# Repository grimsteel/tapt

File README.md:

# tapt

> just a button

`tapt` is a BLE-powered IoT button. It uses an nRF52810 and can be powered for long periods of time on a single CR2032 battery.

It can be connected to Home Assistant and hooked up to automations from there.

## Usage

> Note: do NOT connect the battery when the board is powered on the debug header.

### Assembly

1. The 5 pin debug header must be soldered on for flashing
2. The battery holder can be soldered onto the back 
3. The WS2812B and the UART are optional. Both of these will cause more battery drain.
4. The PCB can be screwed into the base of the case. The button cap locks into the case.

### Flashing

> Note: An nRF-SDK environment is required. This is a *freestanding project*

1. Customize the device ID and board name if needed in `prj.conf`
1. Build the firmware:
   ```sh
   west build -b tapt -- -DBOARD_ROOT=.
   ```
1. Flash the nRF over SWD, using the SWD header on the board. The pins are labeled on the bottom.

   Firmware is included in the `./firmware` directory.
3. Profit. The button should be autodiscovered in Home Assistant, where it will expose a button entity.

## Purpose

I made this because I wanted a large button for controlling random automations.

I also wanted to learn more about RF PCB design, and the nRF chip was a great place to start.

## Schematic + PCB

| F.Cu                         | In1.Cu                       | In2.Cu                       | B.Cu                         |
|------------------------------|------------------------------|------------------------------|------------------------------|
|  |  |  |  |
|                              |                              |                              |                              |

## Case

Apart from the PCB, tapt just has two components: the base and the button. 

The PCB is screwed into the base, and the button sits inside the base. When pressed down, it presses the limit switch.

[Onshape link](https://cad.onshape.com/documents/617a57c855f6b668c2d4cd24/w/013e725e8d7df515c4261645/e/6602b3eddf1a670923f88f78)

## Bill of Materials

[BOM CSV](./bom.csv)

If the price is 0, I have the component already (basically everything except the PCB/PCBA). I added links for reference, though

| Description            | Part ID  | Link                                                 | Per-unit price | Board Quantity | Total Quantity | Extended? | Total Price | Running Price w/ Tax |
|------------------------|----------|------------------------------------------------------|----------------|----------------|----------------|-----------|-------------|----------------------|
| 2.4 GHz Chip Antenna   | C89334   | https://jlcpcb.com/partdetail/C89334                 | $0.62          | 1              | 5              | TRUE      | $6.1630     | $6.69                |
| 100nF Capacitor        | C1525    | https://jlcpcb.com/partdetail/C1525                  | $0.00          | 4              | 8              | FALSE     | $0.0104     | $6.70                |
| 0.8pF Capacitor        | C88902   | https://jlcpcb.com/partdetail/C88902                 | $0.04          | 1              | 20             | TRUE      | $3.7420     | $10.76               |
| 1.0pF Capacitor        | C1550    | https://jlcpcb.com/partdetail/C1550                  | $0.00          | 1              | 20             | FALSE     | $0.0240     | $10.79               |
| 100pF Capacitor        | C1546    | https://jlcpcb.com/partdetail/C1546                  | $0.00          | 1              | 2              | FALSE     | $0.0024     | $10.79               |
| 1uF Capacitor          | C28323   | https://jlcpcb.com/partdetail/C28323                 | $0.01          | 1              | 2              | FALSE     | $0.0254     | $10.82               |
| 12pF Capacitor         | C1547    | https://jlcpcb.com/partdetail/C1547                  | $0.00          | 4              | 8              | FALSE     | $0.0096     | $10.83               |
| 4.7uF Capacitor        | C19666   | https://jlcpcb.com/partdetail/C19666                 | $0.01          | 1              | 2              | FALSE     | $0.0206     | $10.85               |
| Green LED              | C2297    | https://jlcpcb.com/partdetail/C2297                  | $0.02          | 1              | 2              | FALSE     | $0.0314     | $10.88               |
| 3.9nH Inductor         | C14033   | https://jlcpcb.com/partdetail/C14033                 | $0.00          | 2              | 20             | FALSE     | $0.0800     | $10.97               |
| 10uH Inductor          | C86083   | https://jlcpcb.com/partdetail/C86083                 | $0.05          | 1              | 6              | TRUE      | $3.3412     | $14.60               |
| 15nH Inductor          | C27143   | https://jlcpcb.com/partdetail/C27143                 | $0.05          | 1              | 20             | FALSE     | $1.0200     | $15.71               |
| 2.7nH Inductor         | C27123   | https://jlcpcb.com/partdetail/C27123                 | $0.00          | 1              | 20             | TRUE      | $3.1360     | $19.12               |
| 1k Resistor            | C11702   | https://jlcpcb.com/partdetail/C11702                 | $0.00          | 1              | 2              | FALSE     | $0.0014     | $19.12               |
| 100k Resistor          | C25741   | https://jlcpcb.com/partdetail/C25741                 | $0.00          | 1              | 2              | FALSE     | $0.0016     | $19.12               |
| 1M Resistor            | C26083   | https://jlcpcb.com/partdetail/C26083                 | $0.00          | 2              | 4              | FALSE     | $0.0032     | $19.12               |
| SW_SPST Button         | C720477  | https://jlcpcb.com/partdetail/C720477                | $0.05          | 1              | 2              | FALSE     | $0.1082     | $19.24               |
| nRF52810-QCxx          | C519278  | https://jlcpcb.com/partdetail/C519278                | $2.99          | 1              | 2              | TRUE      | $9.0228     | $29.04               |
| 32MHz Crystal          | C2965582 | https://jlcpcb.com/partdetail/C2965582               | $0.07          | 1              | 6              | TRUE      | $3.4606     | $32.80               |
| 32.768kHz Crystal      | C97603   | https://jlcpcb.com/partdetail/C97603                 | $0.24          | 1              | 5              | TRUE      | $4.2365     | $37.40               |
| PCB                    |          |                                                      | $1.00          |                | 2              |           | $2.00       | $39.57               |
| PCBA Fees              |          |                                                      | $11.55         |                | 1              |           | $11.55      | $52.12               |
| PCB Shipping           |          |                                                      | $3.12          |                | 1              |           | $3.12       | $55.51               |
| Case                   |          | 3d-printed                                           | $0.00          |                | 1              |           | $0.00       | $55.51               |
| M3 Heatset             |          | https://www.aliexpress.us/item/3256802711669116.html | $0.00          |                | 2              |           | $0.00       | $55.51               |
| M3 Screw x 8mm         |          | https://www.aliexpress.us/item/2255801013414226.html | $0.00          |                | 2              |           | $0.00       | $55.51               |
| SPDT Limit Switch      |          | https://www.aliexpress.us/item/2255800451734482.html | $0.00          |                | 1              |           | $0.00       | $55.51               |
| 2.54mm Pin Header 1x05 |          | https://www.aliexpress.us/item/3256806247917356.html | $0.00          |                | 1              |           | $0.00       | $55.51               |
| CR2032 Holder          |          | https://www.aliexpress.us/item/3256810117671035.html | $0.00          |                | 1              |           | $0.00       | $55.51               |

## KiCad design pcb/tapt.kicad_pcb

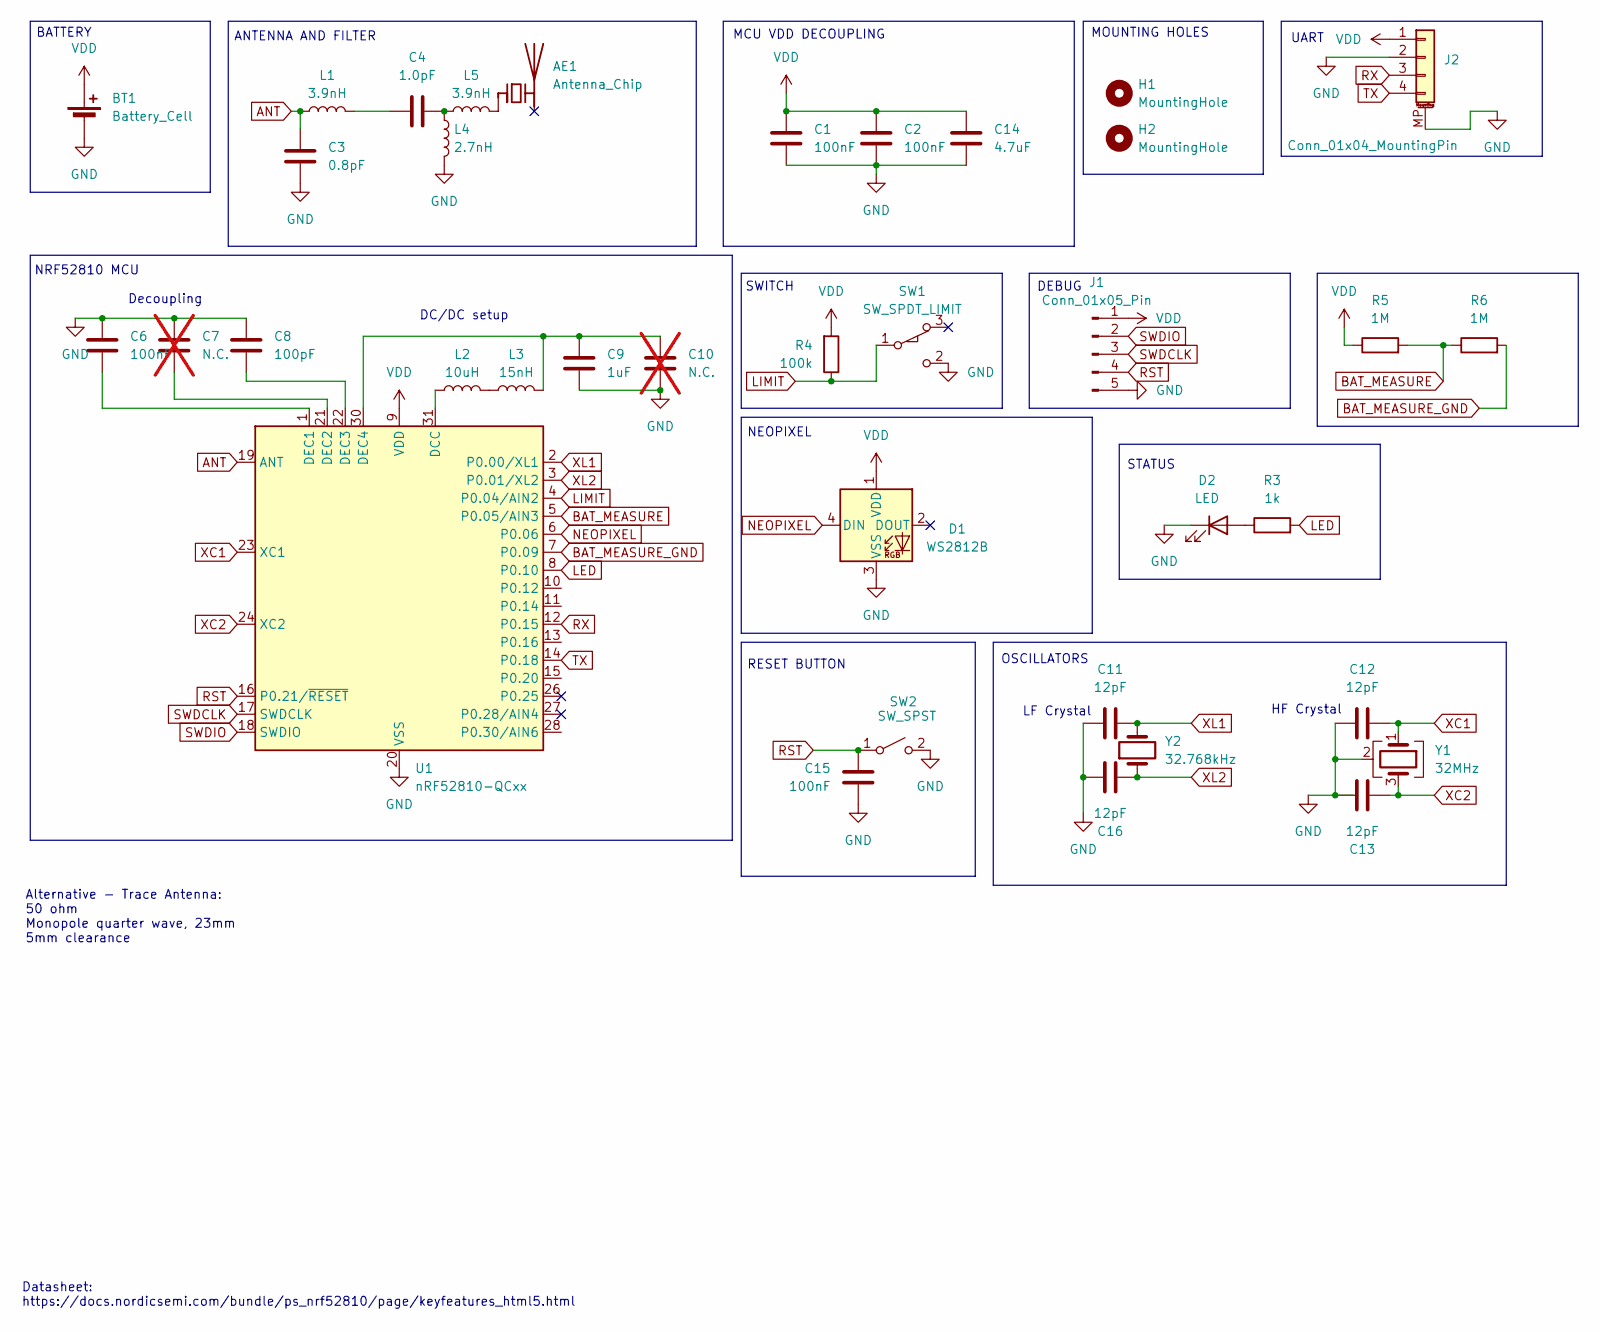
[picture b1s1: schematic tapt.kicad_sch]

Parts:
AE1: Antenna_Chip; L_1206_3216Metric; LCSC C89334
BT1: Battery_Cell; SolderWire-0.5sqmm_1x02_P4.6mm_D0.9mm_OD2.1mm; LCSC C2979167
C1, C2, C6, C15: 100nF; C_0402_1005Metric; LCSC C1525
C3: 0.8pF; C_0402_1005Metric; LCSC C88902
C4: 1.0pF; C_0402_1005Metric; LCSC C1550
C7, C10: N.C.; C_0402_1005Metric; not fitted
C8: 100pF; C_0402_1005Metric; LCSC C1546
C9: 1uF; C_0805_2012Metric; LCSC C28323
C11, C12, C13, C16: 12pF; C_0402_1005Metric; LCSC C1547
C14: 4.7uF; C_0603_1608Metric; LCSC C19666
D1: WS2812B; LED_WS2812B_PLCC4_5.0x5.0mm_P3.2mm
D2: LED; LED_0805_2012Metric; LCSC C2297
H1, H2: MountingHole; MountingHole_3.2mm_M3
J1: Conn_01x05_Pin; PinHeader_1x05_P2.54mm_Vertical
J2: Conn_01x04_MountingPin; JST_SH_BM04B-SRSS-TB_1x04-1MP_P1.00mm_Vertical
L1, L5: 3.9nH; L_0402_1005Metric; LCSC C14033
L2: 10uH; L_0603_1608Metric; LCSC C86083
L3: 15nH; L_0402_1005Metric; LCSC C27143
L4: 2.7nH; L_0402_1005Metric; LCSC C27123
R3: 1k; R_0402_1005Metric; LCSC C11702
R4: 100k; R_0402_1005Metric; LCSC C25741
R5, R6: 1M; R_0402_1005Metric; LCSC C26083
SW1: SW_SPDT_LIMIT; SW_XKB_DM1-16UP-1
SW2: SW_SPST; SW_SPST_TS-1088-xR020; LCSC C720477
U1: nRF52810-QCxx; QFN-32-1EP_5x5mm_P0.5mm_EP3.6x3.6mm; LCSC C519278
Y1: 32MHz; Crystal_SMD_2016-4Pin_2.0x1.6mm; LCSC C2965582
Y2: 32.768kHz; Crystal_SMD_2012-2Pin_2.0x1.2mm; LCSC C97603

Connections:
ANT: C3.1, L1.1, U1.19 (ANT)
BAT_MEASURE: R5.2, R6.1, U1.5 (P0.05/AIN3)
BAT_MEASURE_GND: R6.2, U1.7 (P0.09)
GND: BT1.2 (-), C1.2, C2.2, C3.2, C6.1, C7.1, C8.1, C9.2, C10.2, C11.1, C12.1, C13.1, C14.2, C15.2, C16.1, D1.3 (VSS), D2.1 (K), J1.5, J2.2, J2.MP (MountPin), L4.2, SW1.2 (B), SW2.2 (B), U1.20 (VSS), U1.29 (VSS), U1.33 (VSS), Y1.2 (G), Y1.4 (G)
LED: R3.2, U1.8 (P0.10)
LIMIT: R4.1, SW1.1 (A), U1.4 (P0.04/AIN2)
NEOPIXEL: D1.4 (DIN), U1.6 (P0.06)
unnamed: AE1.1 (FEED), L5.2
unnamed: C4.1, L1.2
unnamed: C4.2, L4.1, L5.1
unnamed: D2.2 (A), R3.1
unnamed: L2.1, L3.2
unnamed: L2.2, U1.31 (DCC)
unnamed: C6.2, U1.1 (DEC1)
unnamed: C7.2, U1.21 (DEC2)
unnamed: C8.2, U1.22 (DEC3)
unnamed: C9.1, C10.1, L3.1, U1.30 (DEC4)
RST: C15.1, J1.4, SW2.1 (A), U1.16 (P0.21/~RESET)
RX: J2.3, U1.12 (P0.15)
SWDCLK: J1.3, U1.17 (SWDCLK)
SWDIO: J1.2, U1.18 (SWDIO)
TX: J2.4, U1.14 (P0.18)
VDD: BT1.1 (+), C1.1, C2.1, C14.1, D1.1 (VDD), J1.1, J2.1, R4.2, R5.1, U1.9 (VDD), U1.25 (VDD), U1.32 (VDD)
XC1: C12.2, U1.23 (XC1), Y1.1
XC2: C13.2, U1.24 (XC2), Y1.3
XL1: C11.2, U1.2 (P0.00/XL1), Y2.2
XL2: C16.2, U1.3 (P0.01/XL2), Y2.1

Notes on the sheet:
DC/DC setup
RESET BUTTON
ANTENNA AND FILTER
Alternative - Trace Antenna: 50 ohm Monopole quarter wave, 23mm 5mm clearance
UART
HF Crystal
MCU VDD DECOUPLING
Decoupling
SWITCH
OSCILLATORS
MOUNTING HOLES
LF Crystal
NEOPIXEL
STATUS
NRF52810 MCU
BATTERY
DEBUG
Datasheet: https://docs.nordicsemi.com/bundle/ps_nrf52810/page/keyfeatures_html5.html

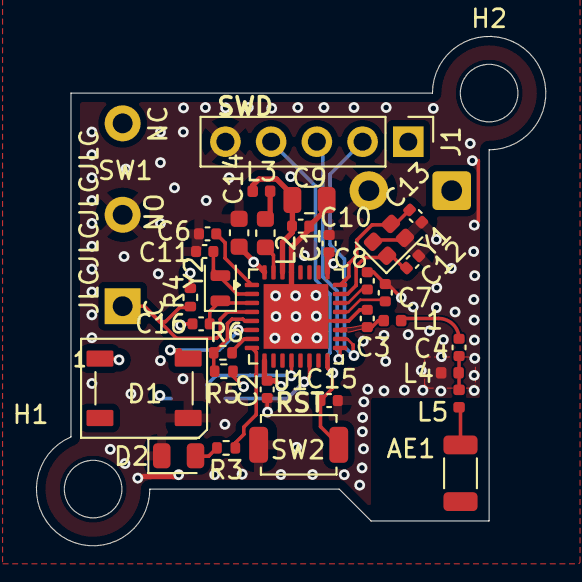
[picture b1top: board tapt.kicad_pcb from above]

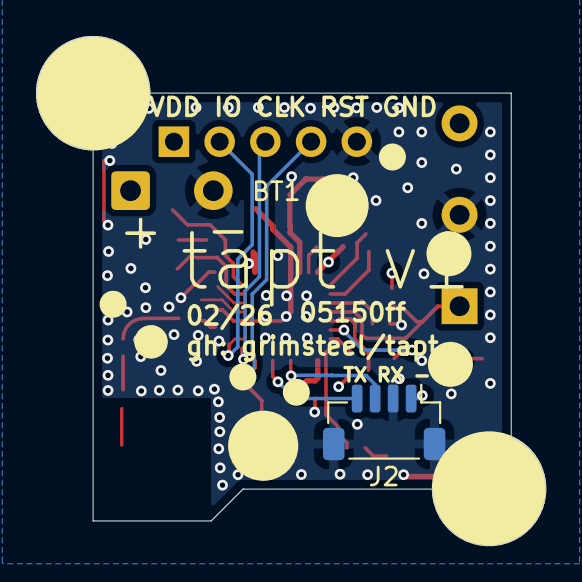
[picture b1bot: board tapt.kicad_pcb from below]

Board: 4 copper layers, 28.3 x 28.3 mm, 37 parts (2 on the bottom side), 27 nets.

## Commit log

2026-01-06 initial schematic
2026-02-14 schematic: antenna, reset button
2026-02-14 pcb: layout and routing
2026-02-14 major rf improvements, battery connector, component relayout
2026-02-14 add mounting holes on dogboned corners
2026-02-15 pcb: silkscreen
2026-02-18 case and readme
2026-02-27 schematic: status led, uart
2026-02-28 pcb: uart, status led
2026-02-28 firmware: initial setup
2026-03-01 pcb: 4 layer redesign, more antenna tuning, low freq crystal
2026-03-07 pcb: clock routing improvements
2026-03-12 firmware: board config, build config, prj.conf
2026-03-12 pcb: battery voltagef divider, hf clock routing
2026-03-15 firmware: finish initial firmware, ble, battery level, device tree
2026-03-15 pcb: voltage divider, antenna t-network
2026-03-15 pcb: minor rf routing improvements
2026-03-16 chore: production files, bom, readme updates
2026-03-16 chore: unignore bom file
2026-03-16 images: improve production renders
2026-03-16 firmware: add unique id
2026-04-02 pcb: impedance matching fixes
2026-04-02 pcb: update production files
2026-04-28 firmware: fix bugs, add detailed build/flash/debug instructions
2026-04-28 chore(pcb): kicad 10 project file updates
